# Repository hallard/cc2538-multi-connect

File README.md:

Zigbee CC2538 + CC2592 Multi Connect Board
==========================================

This is just a quick and dirty PCB breakout board, it could be done better, but the fact is that is does the jobs and it does well. It has been designed with free version of Eagle Cad PCB (V7.7).

The first idea and project was made by @jonoxer with this Z2T aka Zigbee2Tasmota board. You can find original project [here](https://github.com/SuperHouse/Z2T). I won't take any credit on what already done, just used his work (thanks to open source) added new ZigBee chip and some features like:

- Easy to build and solder, 0805 CMS components, the trickiest is the CC2538 module
- just but what you need, not all components are needed (but ZigBee chip CC2538 at least)
- Can works in USB mode, connect to any equiped with USB port CPU (Computer, raspberry, router, ...)
- Can be pluged in Serial mode directly on Raspberry PI
- Can be pluged in Serial mode to any equiped with USB port CPU using FTDI like USB Serial adapturs
- Can be used in standalone mode by adding ESP8266 Wemos Mini D1 board with Tasmota Firmware
- Wired 4 Leds, and 3 are controlled by Z-Stack 3 firmware
- 2 push buttons for Reset / Boot mode (to be able to flash Z-Stack firmware on CC2538)
- JTAG connector (never used)
- SMA footpring for those needed 
- fit on classic Aliexpress cheap enclosures

Detailed Description
====================

This repo is not intented to be a reference for ZigBee stuff and how this ZigBee PCB is working. It's for makers who know what they do with DIY electronic boaards and associated software. Anyway everyone could do and use this board with further reading and some patience.

So there is no specific documentation, but you'll find below some references to start of course, please read carrefelly the following links before opening any issue.

- Starting point [discussion](https://github.com/Koenkk/zigbee2mqtt/discussions/1568) about this module on @Koenkk github
- Tasmota [ZigBee documentation](https://tasmota.github.io/docs/CC2530/)
- @jethome-ru Z-Stack [Firmware](https://github.com/jethome-ru/zigbee-firmware/tree/master/ti/coordinator/cc2538_cc2592) used and instruction to flash

To be honest, the easiest way I found to flash firmware is to use one FTDI USB Serial adapter (take care one with 3.3V regulator, not 5V) and [cc2538prog](https://github.com/1248/cc2538-prog) using WeMos Mini D1 header

Installation
============

Depending on final use you want and I won't describe all here since there is a huge mix of possibilities, I consider after reading, tpi know how and with what you want to use this board.

## Hardware 

- Standalone with WeMos Mini D1
- on Raspberry PI Serial
- on USB computer
- ...

## Sofware

- Tasmota
- ZigBee2Mqtt
- Zigpy
- ...

Schematics
==========

Bill Of Material (BOM)
======================

Nothing fancy, all components are 0805 and/or PTH and can be ordered almost anywhere (digikey, mouser, radiospare, ...). 
use only what you need dependings on what you want to do. 

- This board [PCB](https://oshpark.com/shared_projects/3h5YvEEm) of course 
- cc2538 module take care check the footprint there are differents vendors with different footprints
- R5 any 1K 0805 SMD
- R6 any 1K5 0805 SMD
- C1 33uF (or plus) 1206 tantale capacitor (used one of my boxes, don't know ref)
- 2 x Tactile switch such as SKRPACE010 (4.2x3.2x2.5mm)
- If you want LEDs, 4 SMD 0805 Led plus associated resistor
  - R1 Red = 1K 0805 (Power)
  - R2 Green = 1K 0805 (not used by firmware yet)
  - R3 Blue R3 = 330 ohm 0805 (join mode)
  - R4 Pink or other = 330 Ohm 0805 (ZigBee communication)
- If wanted, PI Connector `2.54 mm 2x5 pin Female Double Row`
- If needed USB Breakout `micro USB to DIP adapter Converter 2,54 mm PCB Breakout`
- If needed 3.3V Regulator `DC 5V to 3.3V Step-Down Power Supply Module AMS1117-3.3` (if powered thru USB without WeMos for Example)
- If needed enclosure `Waterproof Plastic Clear Cover Enclosure Case 85*58*33MM`
- Loved this USB/Serial 3.3V [module](https://aliexpress.com/item/32664922086.html), very cheap and do all job but looks hard to find now, but still available on some places.

Text noted in `between like this one` means type text in google to find seller (Aliexpress, Ebay, ...)

Assembling Boards 
=================

[PCBs.io](https://www.pcbs.io/) was giveing me some reward when ordering my designed boards from their site. This was pretty good, because I useed these rewards to create and design new boards and order boards for a discounted price, but looks like PCBs.io is gone, I do not have any rewards from PCBs.io since August 2020 and my free order placed after are still not received, so my guess they are not on business anymore.

So you can order the board on [oshpark](https://oshpark.com). 

- [V1.0](https://oshpark.com/shared_projects/3h5YvEEm) 

It's a pitty after several discuss with OSHPark that I can't have any rewards for each people ordering my boards, this would allow me to order free PCB for shared projects and create new ones. For information my shared boards generated a total of **$285 162.00** orders at PCBs.io in 4 years, not bad at all :-)

Hoping one day OSHparks will thanks me giving them this market. 

As soldering CC2538 can be tricky, you can just solder needed pin marked with white dot on each. If not using JTAG or LED you can even solder less, check schematics.

Example of Assembled boards 
===========================

**Standalone With WeMos Mini D1**

**In USB Mode (with USB firmware)**

**Packaged into enclosure**

License
=======

I kept the original one so

Copyright 2020 SuperHouse Automation Pty Ltd www.superhouse.tv

The hardware portion of this project is licensed under the TAPR Open Hardware License (www.tapr.org/OHL). The "license" folder within this repository contains a copy of this license in plain text format.

The software portion of this project is licensed under the Simplified BSD License. The "licence" folder within this project contains a copy of this license in plain text format.

Misc
====

See news and other projects on my [blog][1] 
 
[1]: https://hallard.me

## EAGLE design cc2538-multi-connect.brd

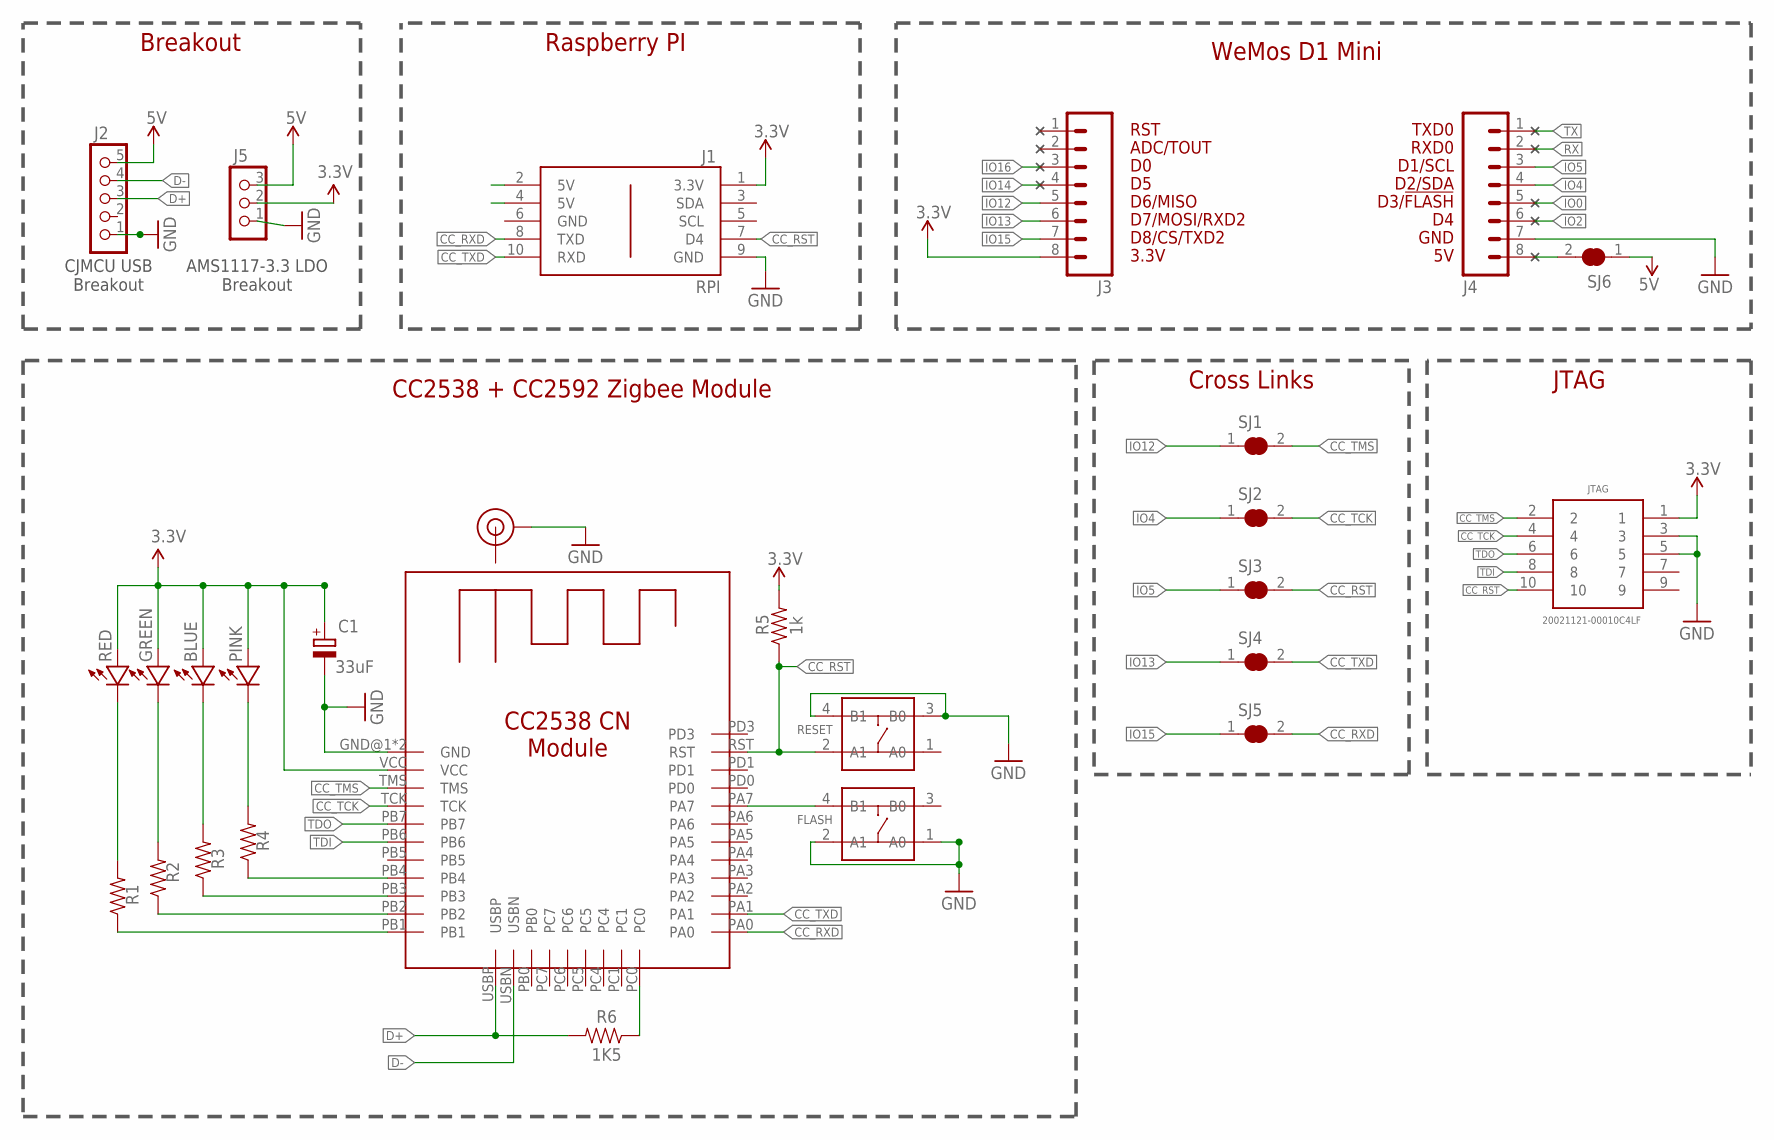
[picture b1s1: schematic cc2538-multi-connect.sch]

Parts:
BLUE: Led; 0805-LED-LARGEPADS
C1: 33uF; A/3216-18W
FLASH: BOOT; SW4-SMD-4.2X3.2X2.5MM
GREEN: Led; 0805-LED-LARGEPADS
J1: RPI; 2X05
J2: CON_HEADER_1X05-PTH; M1X5
J3, J4: M08; 1X08
J5: CON_HEADER_1X03-PTH; M1X3
J$2: ANTENNAEDGE; SMA-EDGE
JTAG: 20021121-00010C4LF; 2002112100010C4LF
PINK: Led; 0805-LED-LARGEPADS
R1, R2, R3, R4: RESISTOR0805-RES; 0805-RES
R5: 1k; 0805-RES
R6: 1K5; 0805-RES
RED: Led; 0805-LED-LARGEPADS
RESET: BOOT; SW4-SMD-4.2X3.2X2.5MM
SJ1, SJ6: D6/P2_1_DD; SJC
SJ2: D2/P2_2_DC; SJC
SJ3: D1/CC_RST; SJC
SJ4: D7/P0_3; SJC
SJ5: D8/P0_2; SJC
U$27: CC2538-CN

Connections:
3.3V: BLUE.PLUS, C1.+, GREEN.PLUS, J1.1 (3.3V), J3.8, J5.2, JTAG.1, PINK.PLUS, R5.2, RED.PLUS, U$27.VCC
5V: J2.5, J5.3, SJ6.1
5V1: J1.2 (5V)
5V2: J1.4 (5V)
5VD1: J4.8, SJ6.2
CC_RST: J1.7 (D4), JTAG.10, R5.1, RESET.2 (A1), SJ3.2, U$27.RST
CC_RXD: J1.8 (TXD), SJ5.2, U$27.PA0
CC_TCK: JTAG.4, SJ2.2, U$27.TCK
CC_TMS: JTAG.2, SJ1.2, U$27.TMS
CC_TXD: J1.10 (RXD), SJ4.2, U$27.PA1
D+: J2.3, R6.2, U$27.USBP
D-: J2.4, U$27.USBN
FLASH: FLASH.4 (B1), U$27.PA7
GND: C1.-, FLASH.1 (A0), FLASH.2 (A1), J1.9 (GND), J2.1, J4.7, J5.1, J$2.GND@1 (GND), J$2.GND@2 (GND), J$2.GND@3 (GND), JTAG.3, JTAG.5, RESET.3 (B0), RESET.4 (B1), U$27.GND@1 (GND), U$27.GND@2 (GND)
IO0: J4.5
IO2: J4.6
IO4: J4.4, SJ2.1
IO5: J4.3, SJ3.1
IO12: J3.5, SJ1.1
IO13: J3.6, SJ4.1
IO14: J3.4
IO15: J3.7, SJ5.1
IO16: J3.3
unnamed: BLUE.MINUS, R3.2
unnamed: R1.1, U$27.PB1
unnamed: R2.1, U$27.PB2
unnamed: R3.1, U$27.PB3
unnamed: R4.1, U$27.PB4
unnamed: PINK.MINUS, R4.2
unnamed: GREEN.MINUS, R2.2
unnamed: R1.2, RED.MINUS
unnamed: R6.1, U$27.PC0
RX: J4.2
TDI: JTAG.8, U$27.PB6
TDO: JTAG.6, U$27.PB7
TX: J4.1

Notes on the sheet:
D3/!FLASH
D6/MISO
D2/SDA
D1/SCL
RXD0
TXD0
D7/MOSI/RXD2
D8/CS/TXD2
ADC/TOUT
GND
3.3V
RST
Cross Links
CC2538 + CC2592 Zigbee Module
WeMos D1 Mini
JTAG
AMS1117-3.3 LDO Breakout
CJMCU USB Breakout
Breakout
Raspberry PI

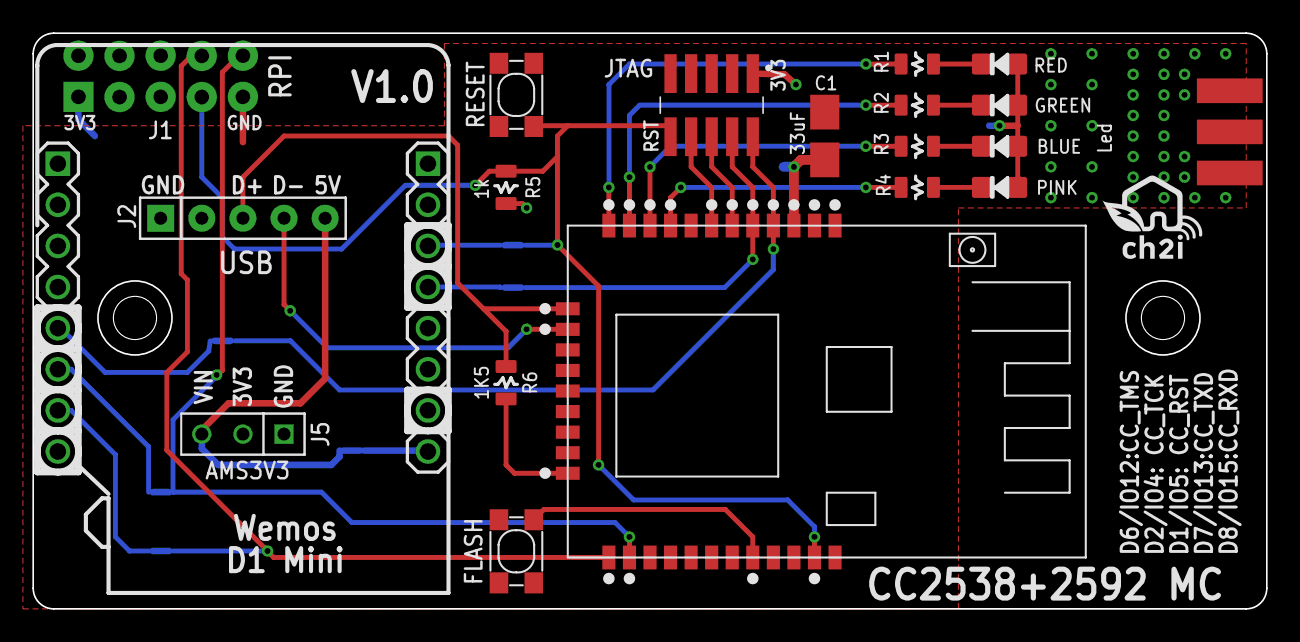
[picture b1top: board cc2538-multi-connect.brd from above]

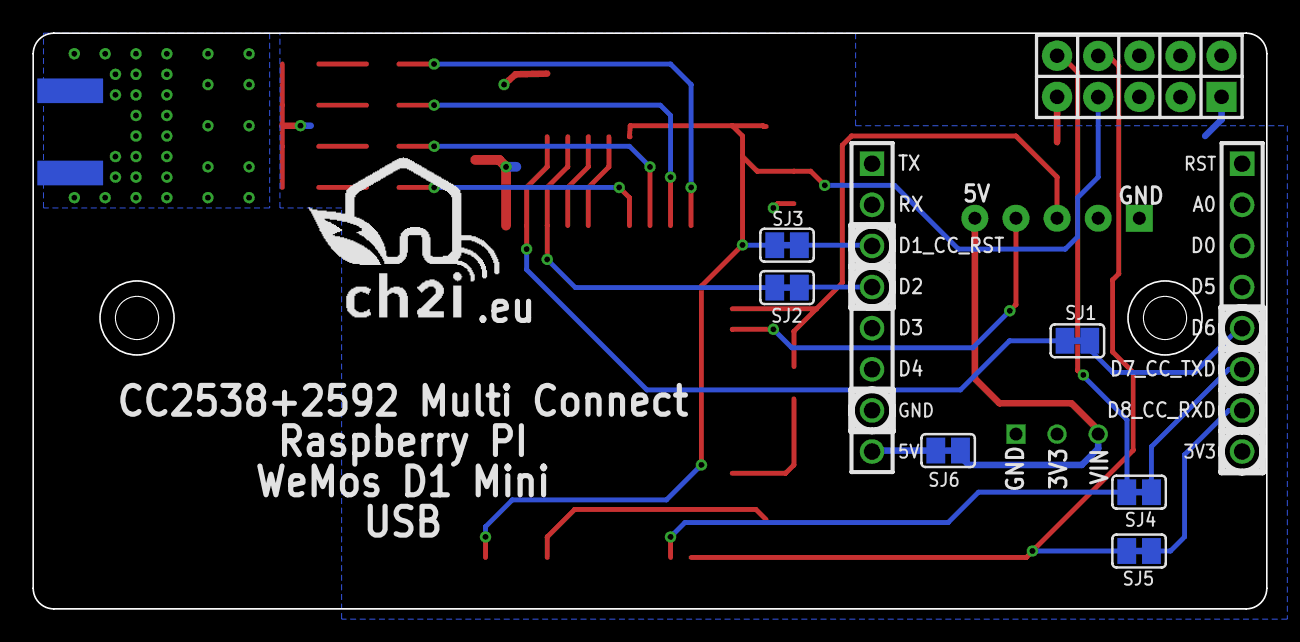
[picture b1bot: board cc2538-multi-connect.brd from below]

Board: 2 copper layers, 76.2 x 35.6 mm, 29 parts (7 on the bottom side), 28 nets.

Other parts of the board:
U$8: LOGO_C2I_015
U$9: LOGO_CH2I_110MM

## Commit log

2021-02-16 creation
2021-02-16 Fixed board link
2021-02-16 fixed links
2021-02-16 Fixed branch on lnks
2021-02-16 renamed jpeg to jpg

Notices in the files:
parts and their libraries:
freetronics-original: Licensing: CC v3.0 Share-Alike You are welcome to use this library for commercial purposes.
